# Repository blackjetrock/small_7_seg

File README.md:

# Small 7 segent LED module

This is a fifteen digit seven segment display made form a PCB with SMD LEDs on it and a 3D printed frme to form the segments. A diffuser is needed over the top of the frame to even the light over the segment.

This construction is similar to larger displays that can be bought, it's just a bit smaller and more dense in terms of the number of digits. The PCB is about 60mm wide and 14mm high. The PCB was hand assembled and then soldered in a reflow oven, but it should be possible to get it assembled by a PCB manufacturer. The LEDs are red. There's no filter. The display looks a lot better in real life than in the photos, it's very difficult to photograph this display. The diffuser is a piece of masking tape stuck over the display at the moment, this also holds the frame on to the PCB, That coud be tidied up.

The frame is 3D printed from resin. This is a white version (which doesn't work):

The white resin doesn't block light well enough, a black resin version is used on the frame attached to the prototype.

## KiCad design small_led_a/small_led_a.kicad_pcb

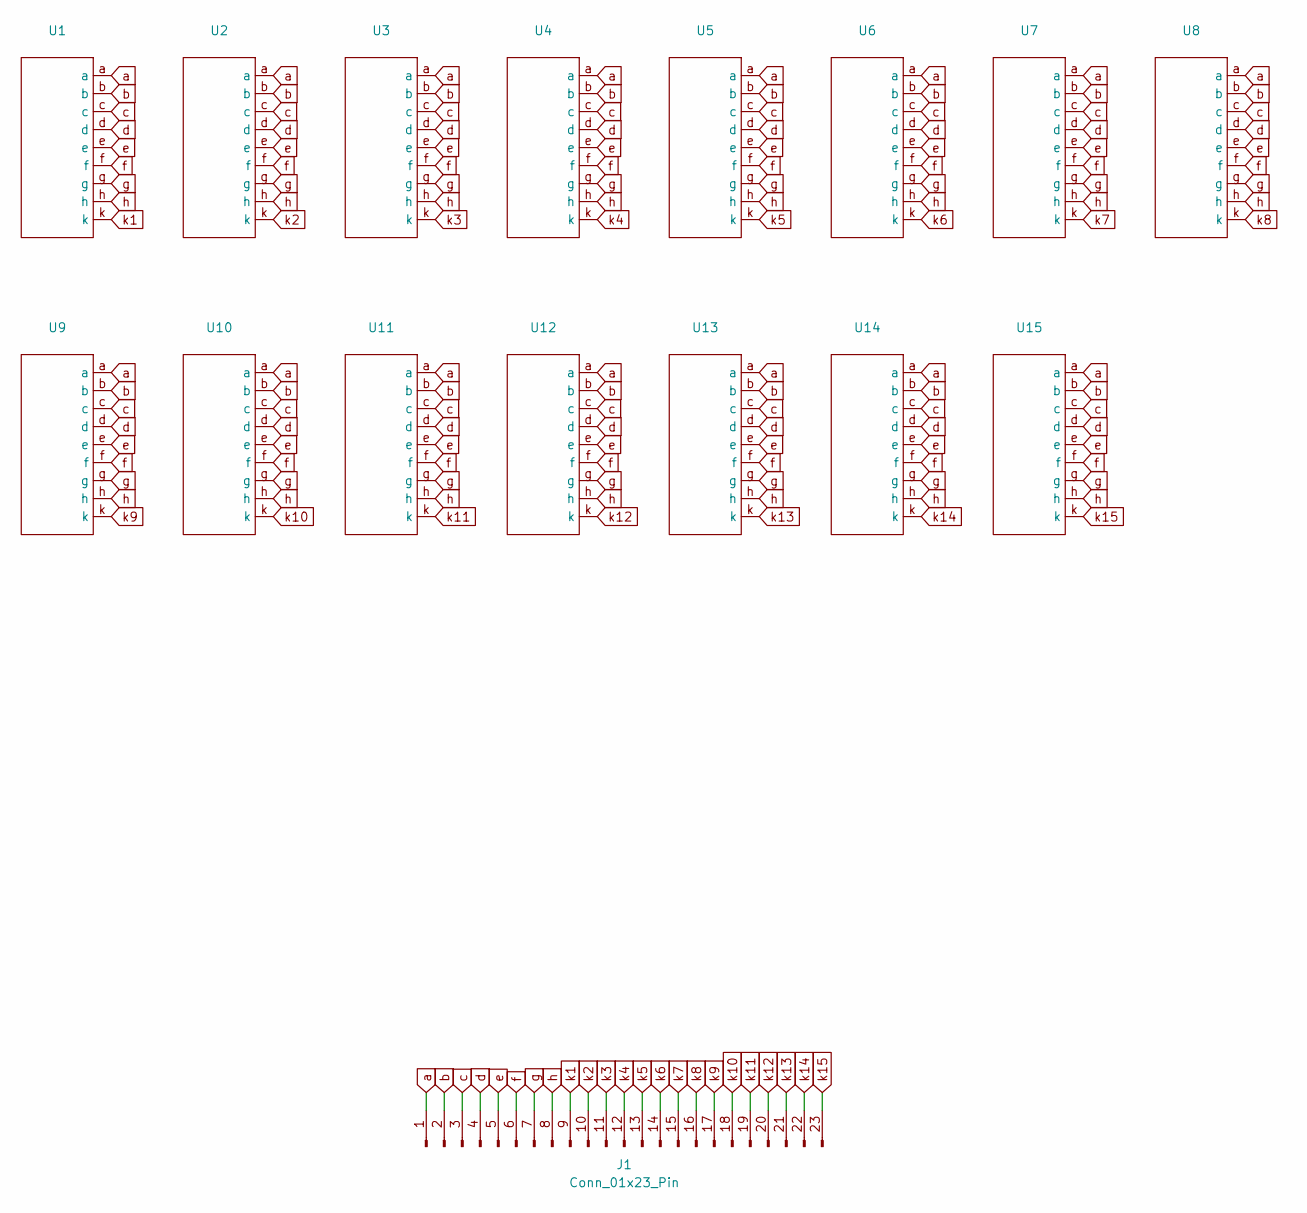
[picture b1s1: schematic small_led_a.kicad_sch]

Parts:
J1: Conn_01x23_Pin; PinHeader_1x23_P1.27mm_Vertical
U1, U2, U3, U4, U5, U6, U7, U8, U9, U10, U11, U12, U13, U14, U15: seg7_0402

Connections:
a: J1.1, U1.a, U2.a, U3.a, U4.a, U5.a, U6.a, U7.a, U8.a, U9.a, U10.a, U11.a, U12.a, U13.a, U14.a, U15.a
b: J1.2, U1.b, U2.b, U3.b, U4.b, U5.b, U6.b, U7.b, U8.b, U9.b, U10.b, U11.b, U12.b, U13.b, U14.b, U15.b
c: J1.3, U1.c, U2.c, U3.c, U4.c, U5.c, U6.c, U7.c, U8.c, U9.c, U10.c, U11.c, U12.c, U13.c, U14.c, U15.c
d: J1.4, U1.d, U2.d, U3.d, U4.d, U5.d, U6.d, U7.d, U8.d, U9.d, U10.d, U11.d, U12.d, U13.d, U14.d, U15.d
e: J1.5, U1.e, U2.e, U3.e, U4.e, U5.e, U6.e, U7.e, U8.e, U9.e, U10.e, U11.e, U12.e, U13.e, U14.e, U15.e
f: J1.6, U1.f, U2.f, U3.f, U4.f, U5.f, U6.f, U7.f, U8.f, U9.f, U10.f, U11.f, U12.f, U13.f, U14.f, U15.f
g: J1.7, U1.g, U2.g, U3.g, U4.g, U5.g, U6.g, U7.g, U8.g, U9.g, U10.g, U11.g, U12.g, U13.g, U14.g, U15.g
h: J1.8, U1.h, U2.h, U3.h, U4.h, U5.h, U6.h, U7.h, U8.h, U9.h, U10.h, U11.h, U12.h, U13.h, U14.h, U15.h
k1: J1.9, U1.k
k2: J1.10, U2.k
k3: J1.11, U3.k
k4: J1.12, U4.k
k5: J1.13, U5.k
k6: J1.14, U6.k
k7: J1.15, U7.k
k8: J1.16, U8.k
k9: J1.17, U9.k
k10: J1.18, U10.k
k11: J1.19, U11.k
k12: J1.20, U12.k
k13: J1.21, U13.k
k14: J1.22, U14.k
k15: J1.23, U15.k

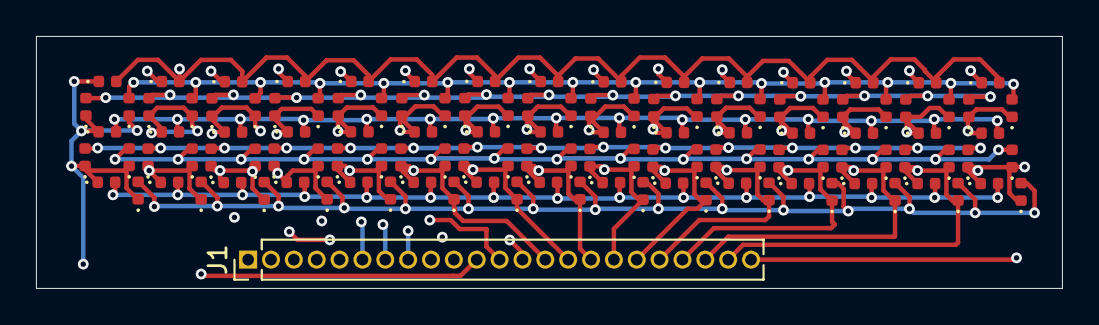
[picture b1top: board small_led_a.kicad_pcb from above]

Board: 4 copper layers, 57.0 x 14.0 mm, 16 parts (0 on the bottom side), 23 nets.
